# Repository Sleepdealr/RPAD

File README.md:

This work is licensed under a **Creative Commons Attribution-NonCommercial-ShareAlike 4.0 International License**.

# RPAD
A macropad designed using the RP2040

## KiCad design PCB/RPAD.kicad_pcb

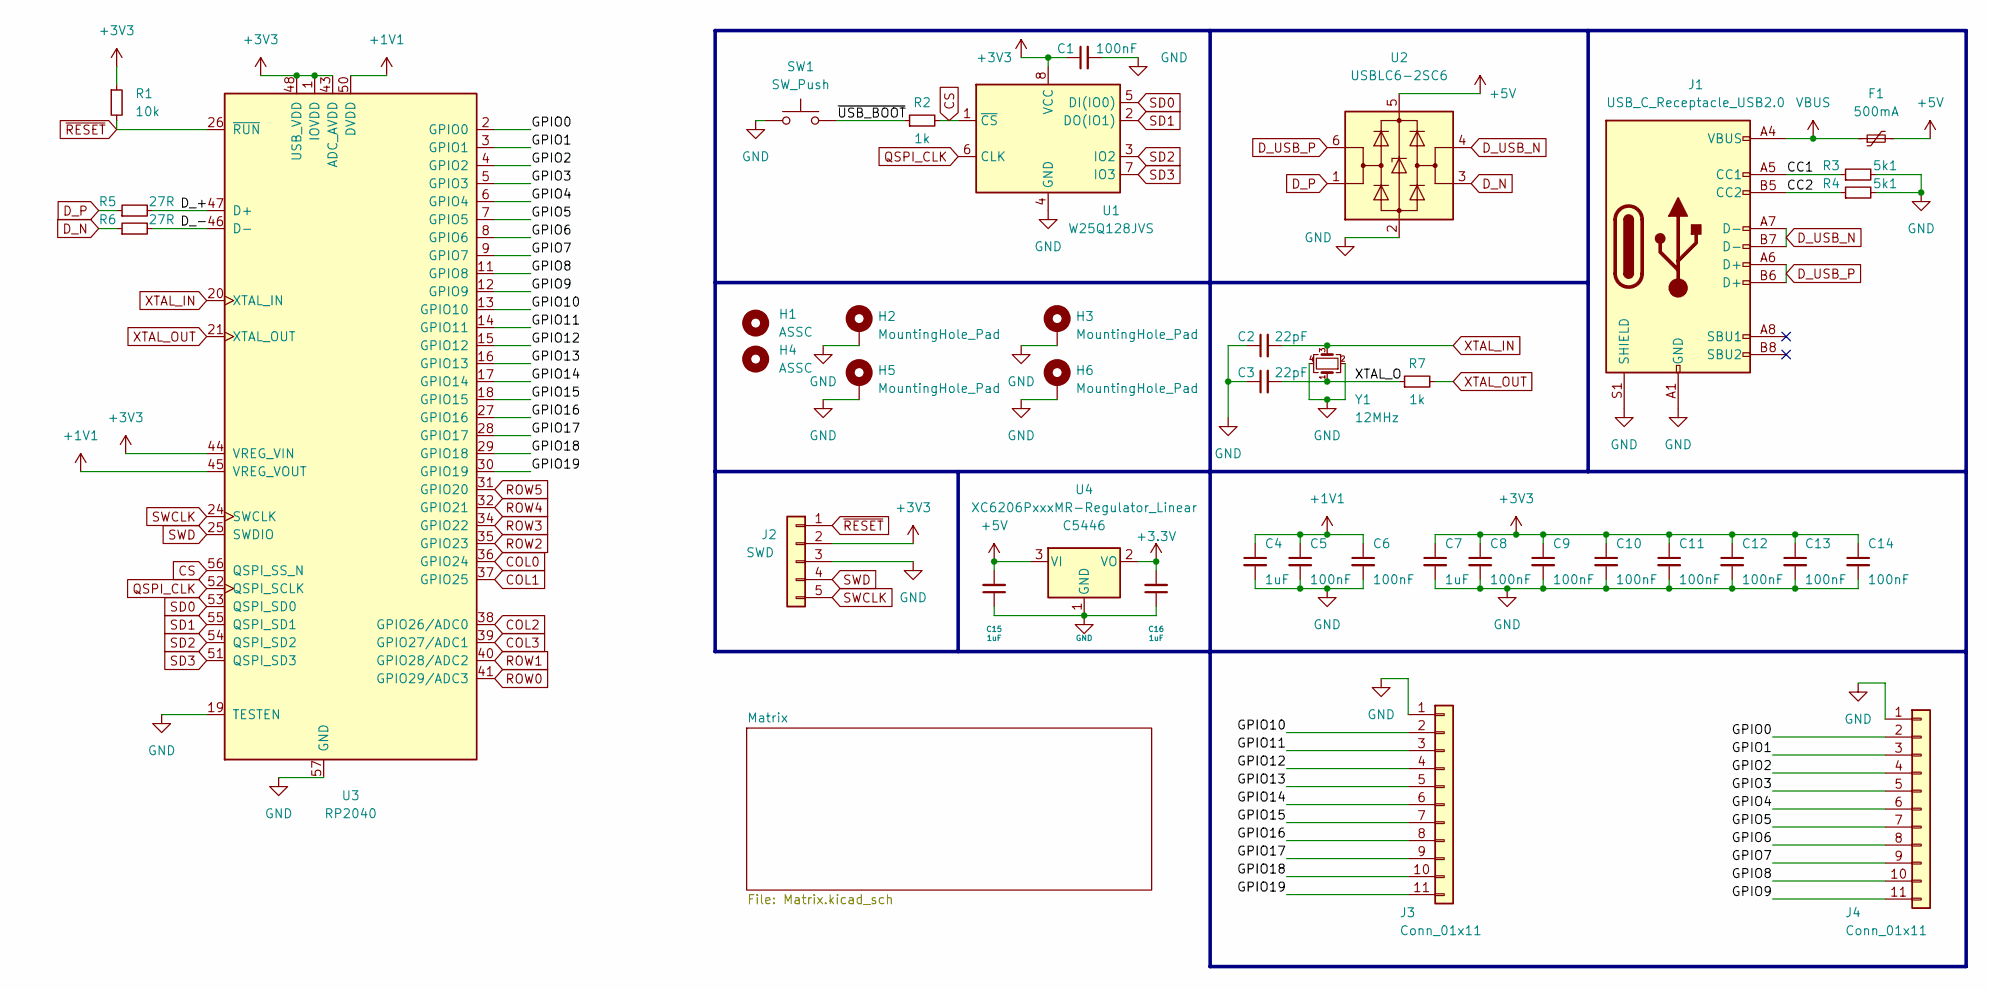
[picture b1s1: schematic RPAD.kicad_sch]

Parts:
C1, C5, C6, C8, C9, C10, C11, C12, C13, C14: 100nF; C_0402_1005Metric; LCSC C1525
C2, C3: 22pF; C_0402_1005Metric; LCSC C1555
C4, C7, C15, C16: 1uF; C_0402_1005Metric; LCSC C52923
F1: 500mA; Fuse_1206_3216Metric; LCSC C70076
H1, H4: ASSC; assc
H2, H3, H5, H6: MountingHole_Pad; MountingHole_2.2mm_M2_Pad
J1: USB_C_Receptacle_USB2.0; USB_C_Receptacle_HRO_TYPE-C-31-M-12; LCSC C165948
J2: SWD; PinSocket_1x05_P2.54mm_Vertical
J3, J4: Conn_01x11; PinSocket_1x11_P2.54mm_Vertical
R1: 10k; R_0402_1005Metric; LCSC C25744
R2, R7: 1k; R_0402_1005Metric; LCSC C11702
R3, R4: 5k1; R_0402_1005Metric; LCSC C25905
R5, R6: 27R; R_0603_1608Metric; LCSC C25190
SW1: SW_Push; PinSocket_1x02_P2.54mm_Vertical
U1: W25Q128JVS; SOIC-8_5.23x5.23mm_P1.27mm; LCSC C131025
U2: USBLC6-2SC6; SOT-23-6; LCSC C2827654
U3: RP2040; RP2040-QFN-56; LCSC C2040
U4: XC6206PxxxMR-Regulator_Linear; SOT-23; LCSC C5446
Y1: 12MHz; Crystal_SMD_3225-4Pin_3.2x2.5mm; LCSC C97242

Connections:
+1V1: C4.1, C5.1, C6.1, U3.23 (DVDD), U3.45 (VREG_VOUT), U3.50 (DVDD)
+5V: C15.2, F1.2, U2.5 (VBUS), U4.3 (VI)
/CC1: J1.A5 (CC1), R3.1
/CC2: J1.B5 (CC2), R4.1
/D_+: R5.2, U3.47 (D+)
/D_-: R6.2, U3.46 (D-)
/GPIO0: J4.2, U3.2 (GPIO0)
/GPIO1: J4.3, U3.3 (GPIO1)
/GPIO2: J4.4, U3.4 (GPIO2)
/GPIO3: J4.5, U3.5 (GPIO3)
/GPIO4: J4.6, U3.6 (GPIO4)
/GPIO5: J4.7, U3.7 (GPIO5)
/GPIO6: J4.8, U3.8 (GPIO6)
/GPIO7: J4.9, U3.9 (GPIO7)
/GPIO8: J4.10, U3.11 (GPIO8)
/GPIO9: J4.11, U3.12 (GPIO9)
/GPIO10: J3.2, U3.13 (GPIO10)
/GPIO11: J3.3, U3.14 (GPIO11)
/GPIO12: J3.4, U3.15 (GPIO12)
/GPIO13: J3.5, U3.16 (GPIO13)
/GPIO14: J3.6, U3.17 (GPIO14)
/GPIO15: J3.7, U3.18 (GPIO15)
/GPIO16: J3.8, U3.27 (GPIO16)
/GPIO17: J3.9, U3.28 (GPIO17)
/GPIO18: J3.10, U3.29 (GPIO18)
/GPIO19: J3.11, U3.30 (GPIO19)
/XTAL_O: C3.2, R7.1, Y1.1
/~USB_BOOT: R2.1, SW1.2
COL0: U3.36 (GPIO24); also elsewhere on the board
COL1: U3.37 (GPIO25); also elsewhere on the board
COL2: U3.38 (GPIO26/ADC0); also elsewhere on the board
COL3: U3.39 (GPIO27/ADC1); also elsewhere on the board
CS: R2.2, U1.1 (~CS), U3.56 (QSPI_SS_N)
D_N: R6.1, U2.3 (I/O2)
D_P: R5.1, U2.1 (I/O1)
D_USB_N: J1.A7 (D-), J1.B7 (D-), U2.4 (I/O2)
D_USB_P: J1.A6 (D+), J1.B6 (D+), U2.6 (I/O1)
GND: C1.2, C2.1, C3.1, C4.2, C5.2, C6.2, C7.2, C8.2, C9.2, C10.2, C11.2, C12.2, C13.2, C14.2, C15.1, C16.1, H2.1, H3.1, H5.1, H6.1, J1.A1 (GND), J1.A12 (GND), J1.B1 (GND), J1.B12 (GND), J1.S1 (SHIELD), J2.3, J3.1, J4.1, R3.2, R4.2, SW1.1, U1.4 (GND), U2.2 (GND), U3.19 (TESTEN), U3.57 (GND), U4.1 (GND), Y1.2, Y1.4
QSPI_CLK: U1.6 (CLK), U3.52 (QSPI_SCLK)
ROW0: U3.41 (GPIO29/ADC3); also elsewhere on the board
ROW1: U3.40 (GPIO28/ADC2); also elsewhere on the board
ROW2: U3.35 (GPIO23); also elsewhere on the board
ROW3: U3.34 (GPIO22); also elsewhere on the board
ROW4: U3.32 (GPIO21); also elsewhere on the board
ROW5: U3.31 (GPIO20); also elsewhere on the board
SD0: U1.5 (DI(IO0)), U3.53 (QSPI_SD0)
SD1: U1.2 (DO(IO1)), U3.55 (QSPI_SD1)
SD2: U1.3 (IO2), U3.54 (QSPI_SD2)
SD3: U1.7 (IO3), U3.51 (QSPI_SD3)
SWCLK: J2.5, U3.24 (SWCLK)
SWD: J2.4, U3.25 (SWDIO)
VBUS: F1.1, J1.A4 (VBUS), J1.A9 (VBUS), J1.B4 (VBUS), J1.B9 (VBUS)
XTAL_IN: C2.2, U3.20 (XTAL_IN), Y1.3
XTAL_OUT: R7.2, U3.21 (XTAL_OUT)
~RESET: J2.1, R1.2, U3.26 (~RUN)

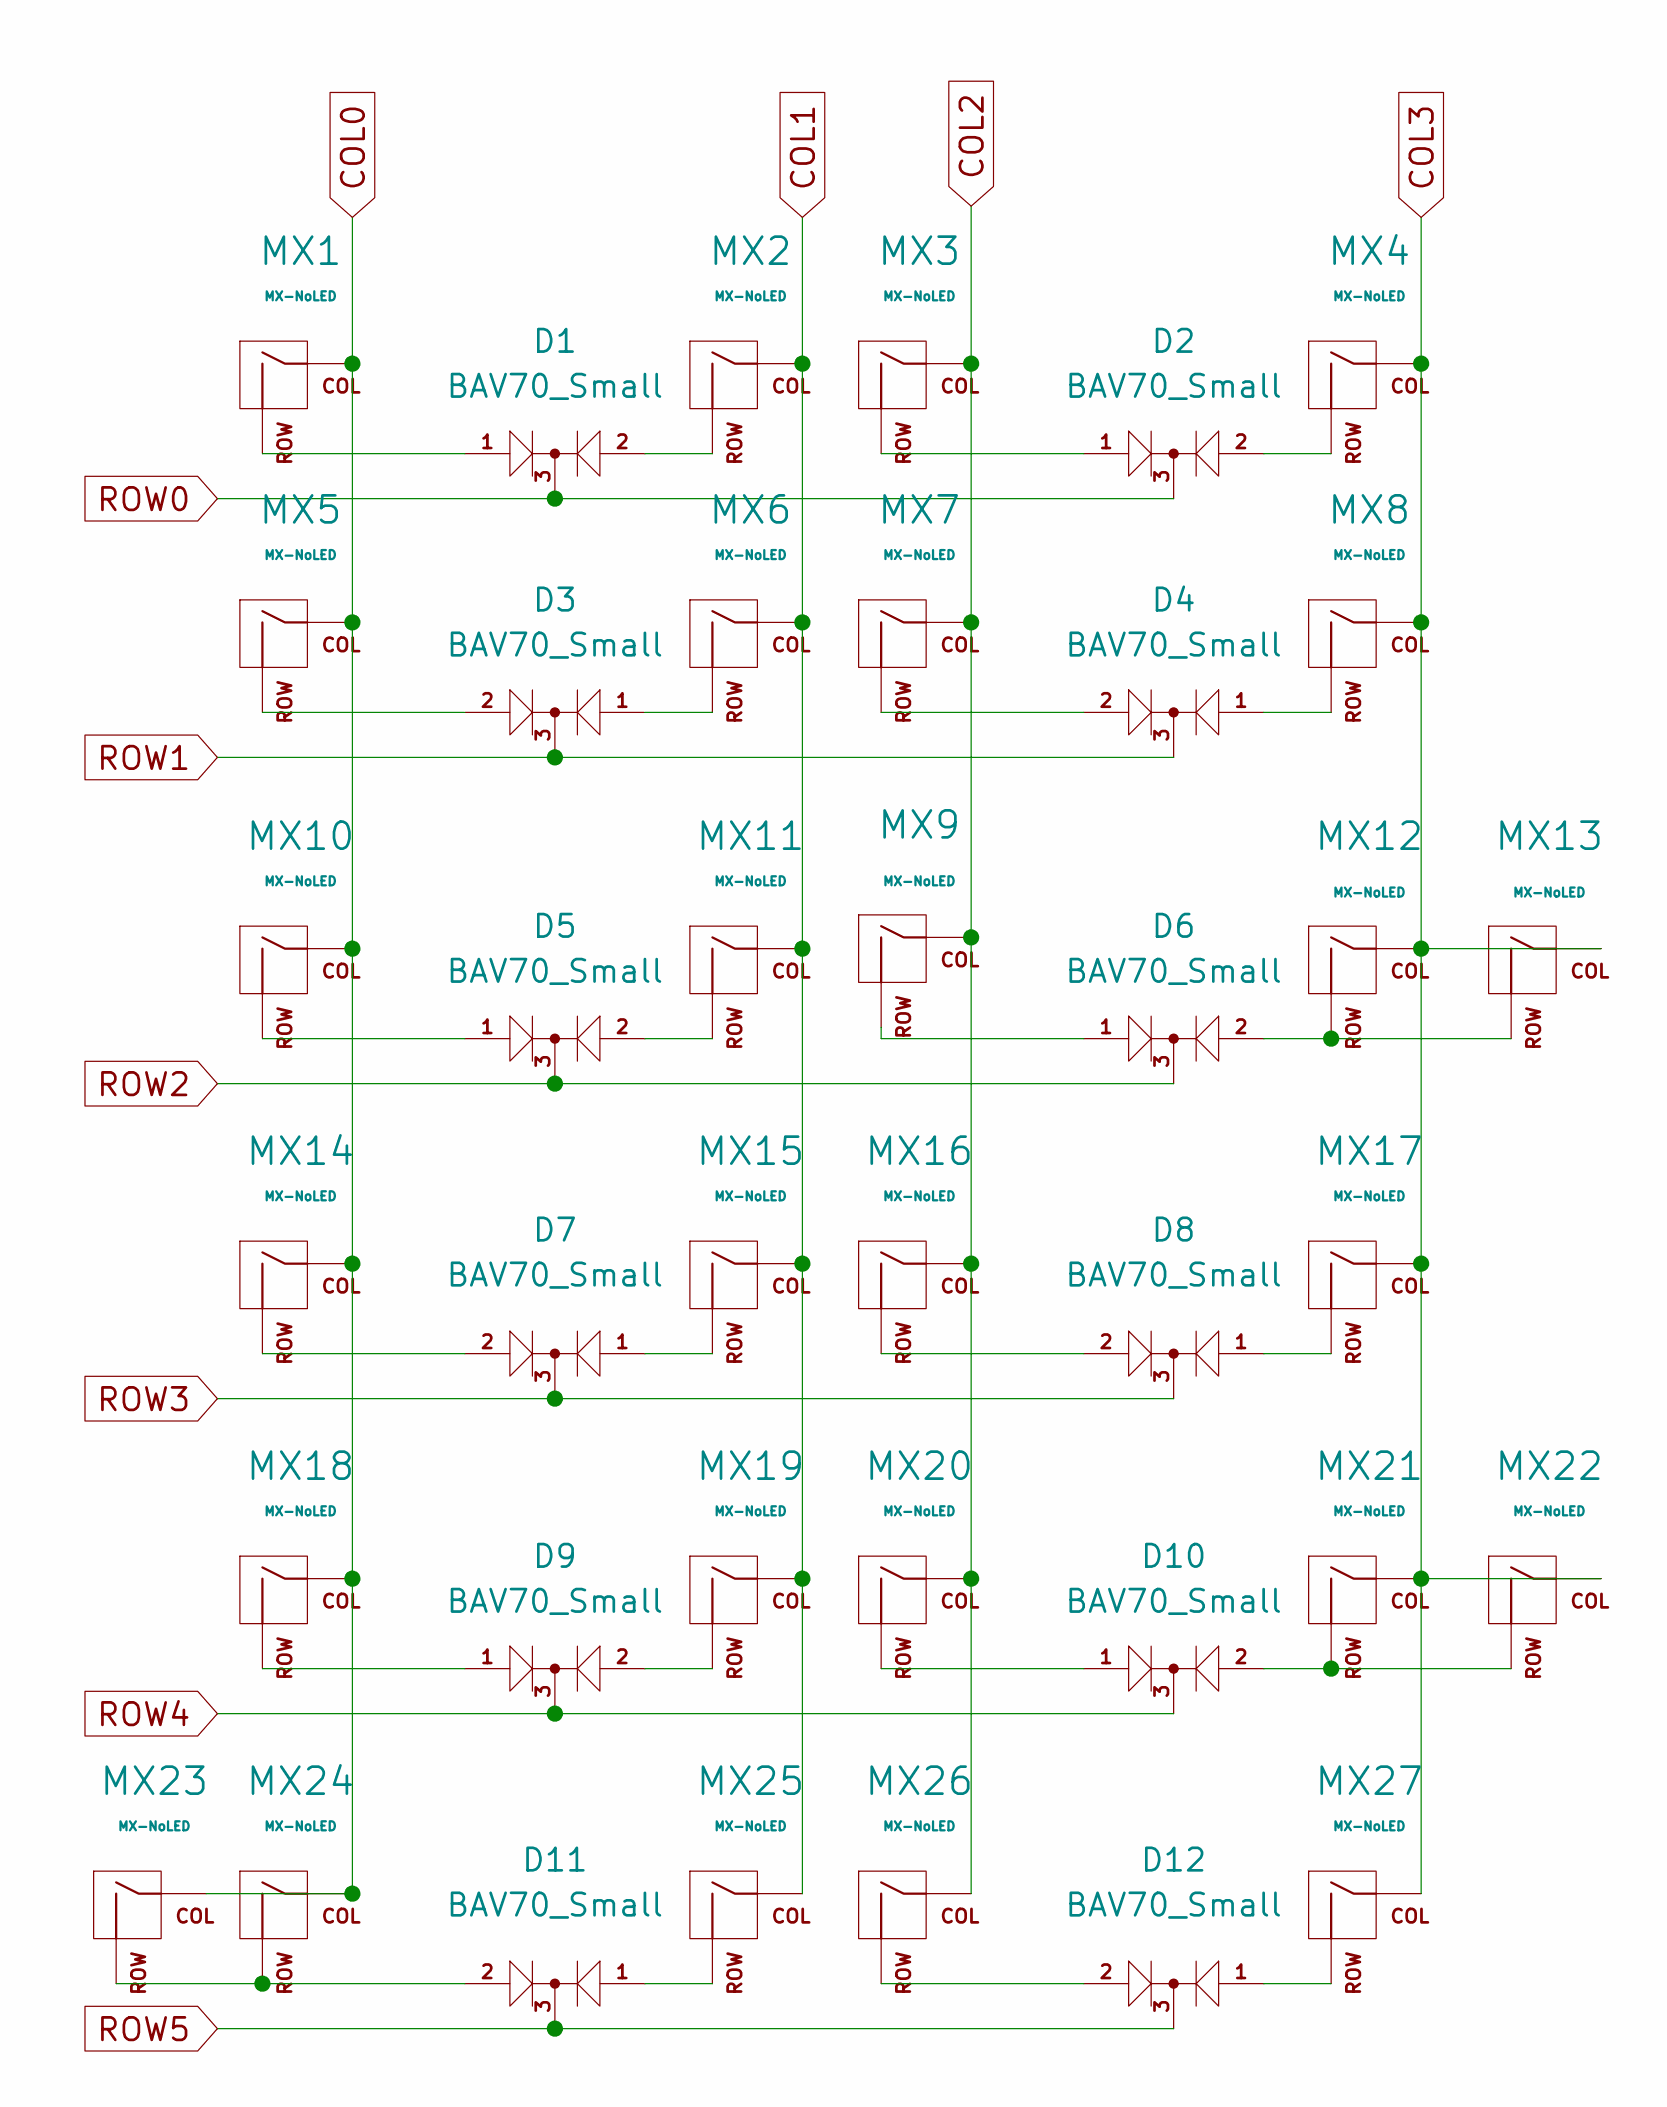
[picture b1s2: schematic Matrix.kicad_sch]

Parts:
D1, D2, D3, D4, D5, D6, D7, D8, D9, D10, D11, D12: BAV70_Small; SOT-23; LCSC C68978
MX1, MX2, MX3, MX4, MX5, MX6, MX7, MX8, MX9, MX10, MX11, MX12, MX14, MX15, MX16, MX17, MX18, MX19, MX20, MX21, MX24, MX25, MX26, MX27: MX-NoLED; MXOnly-1U-NoLED
MX13, MX22: MX-NoLED; MXOnly-2U-VerticalStabilizers-NoLED
MX23: MX-NoLED; MXOnly-2U-ReversedStabilizers-NoLED

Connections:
COL0: MX1.1 (COL), MX5.1 (COL), MX10.1 (COL), MX14.1 (COL), MX18.1 (COL), MX23.1 (COL), MX24.1 (COL); also elsewhere on the board
COL1: MX2.1 (COL), MX6.1 (COL), MX11.1 (COL), MX15.1 (COL), MX19.1 (COL), MX25.1 (COL); also elsewhere on the board
COL2: MX3.1 (COL), MX7.1 (COL), MX9.1 (COL), MX16.1 (COL), MX20.1 (COL), MX26.1 (COL); also elsewhere on the board
COL3: MX4.1 (COL), MX8.1 (COL), MX12.1 (COL), MX13.1 (COL), MX17.1 (COL), MX21.1 (COL), MX22.1 (COL), MX27.1 (COL); also elsewhere on the board
unnamed: D1.1 (A1), MX1.2 (ROW)
unnamed: D1.2 (A2), MX2.2 (ROW)
unnamed: D2.1 (A1), MX3.2 (ROW)
unnamed: D2.2 (A2), MX4.2 (ROW)
unnamed: D3.1 (A1), MX6.2 (ROW)
unnamed: D3.2 (A2), MX5.2 (ROW)
unnamed: D4.1 (A1), MX8.2 (ROW)
unnamed: D4.2 (A2), MX7.2 (ROW)
unnamed: D5.1 (A1), MX10.2 (ROW)
unnamed: D5.2 (A2), MX11.2 (ROW)
unnamed: D6.1 (A1), MX9.2 (ROW)
unnamed: D6.2 (A2), MX12.2 (ROW), MX13.2 (ROW)
unnamed: D7.1 (A1), MX15.2 (ROW)
unnamed: D7.2 (A2), MX14.2 (ROW)
unnamed: D8.1 (A1), MX17.2 (ROW)
unnamed: D8.2 (A2), MX16.2 (ROW)
unnamed: D9.1 (A1), MX18.2 (ROW)
unnamed: D9.2 (A2), MX19.2 (ROW)
unnamed: D10.1 (A1), MX20.2 (ROW)
unnamed: D10.2 (A2), MX21.2 (ROW), MX22.2 (ROW)
unnamed: D11.1 (A1), MX25.2 (ROW)
unnamed: D11.2 (A2), MX23.2 (ROW), MX24.2 (ROW)
unnamed: D12.1 (A1), MX27.2 (ROW)
unnamed: D12.2 (A2), MX26.2 (ROW)
ROW0: D1.3 (K), D2.3 (K); also elsewhere on the board
ROW1: D3.3 (K), D4.3 (K); also elsewhere on the board
ROW2: D5.3 (K), D6.3 (K); also elsewhere on the board
ROW3: D7.3 (K), D8.3 (K); also elsewhere on the board
ROW4: D9.3 (K), D10.3 (K); also elsewhere on the board
ROW5: D11.3 (K), D12.3 (K); also elsewhere on the board

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
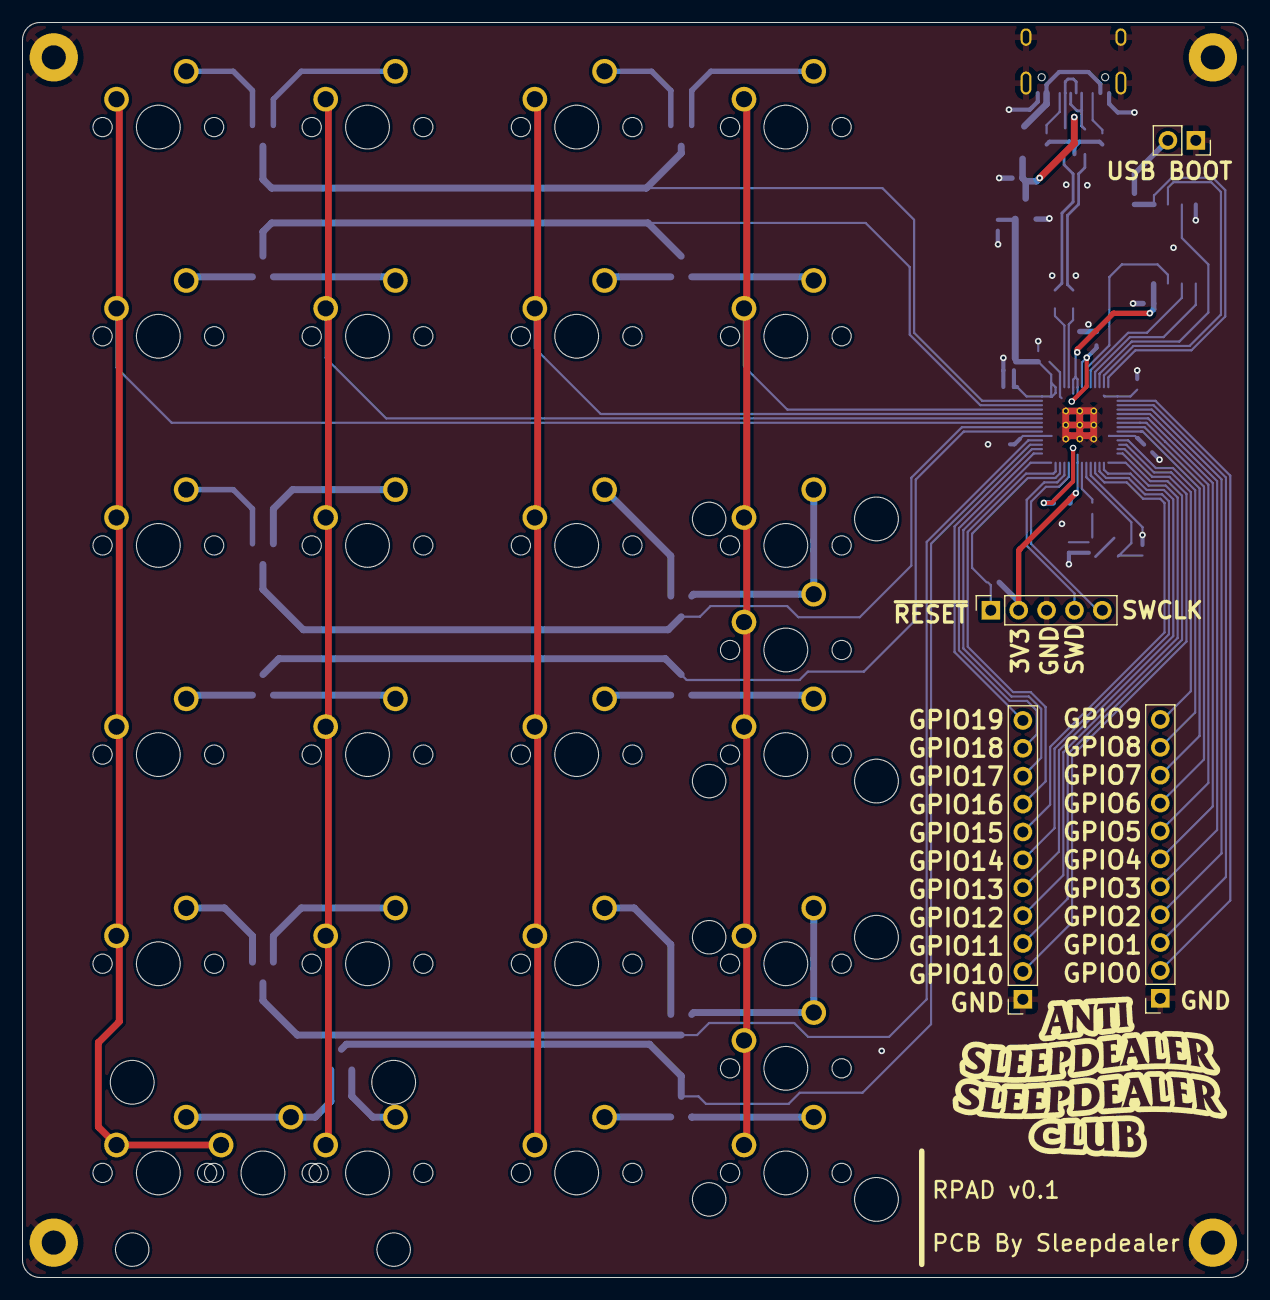
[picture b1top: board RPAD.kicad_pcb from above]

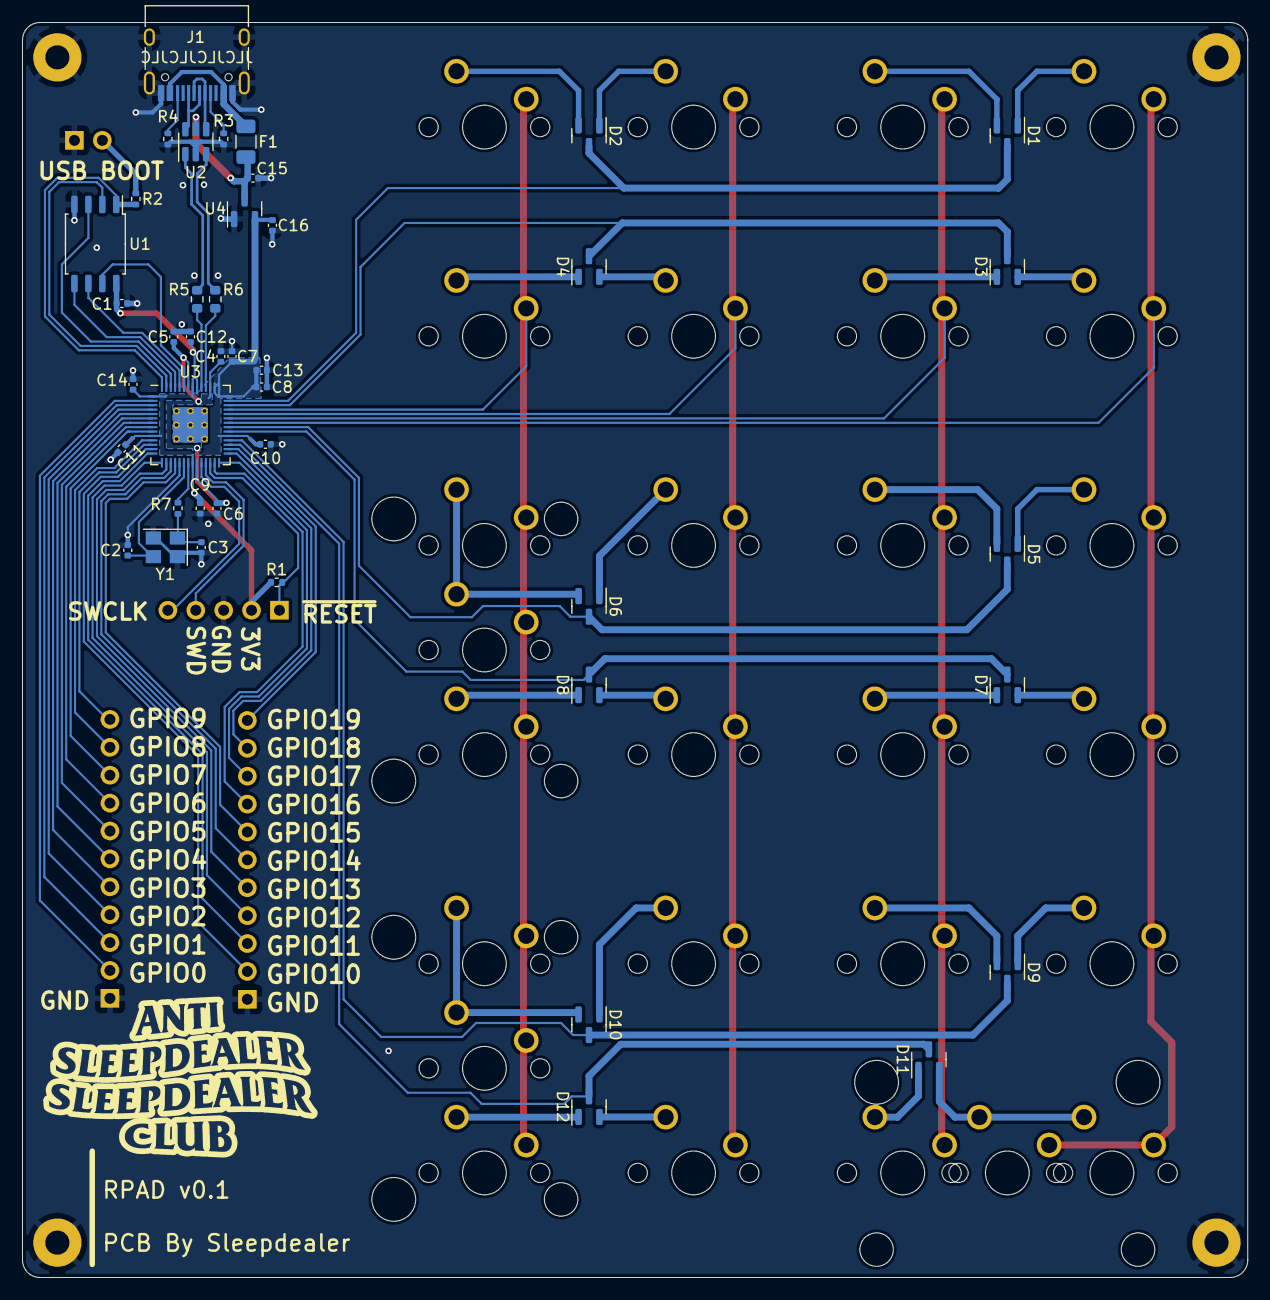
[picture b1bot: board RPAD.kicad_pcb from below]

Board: 2 copper layers, 111.6 x 114.3 mm, 79 parts (43 on the bottom side), 80 nets.

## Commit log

2021-12-07 Init PCB and Readme
2021-12-07 Add Firmware
2021-12-08 Fix readme and libraries
2021-12-08 Fix stupid borked reamde
2021-12-08 Update Reame
2021-12-08 Add license
2021-12-18 Add image

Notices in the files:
README.md:
CC BY-NC-SA 4.0
